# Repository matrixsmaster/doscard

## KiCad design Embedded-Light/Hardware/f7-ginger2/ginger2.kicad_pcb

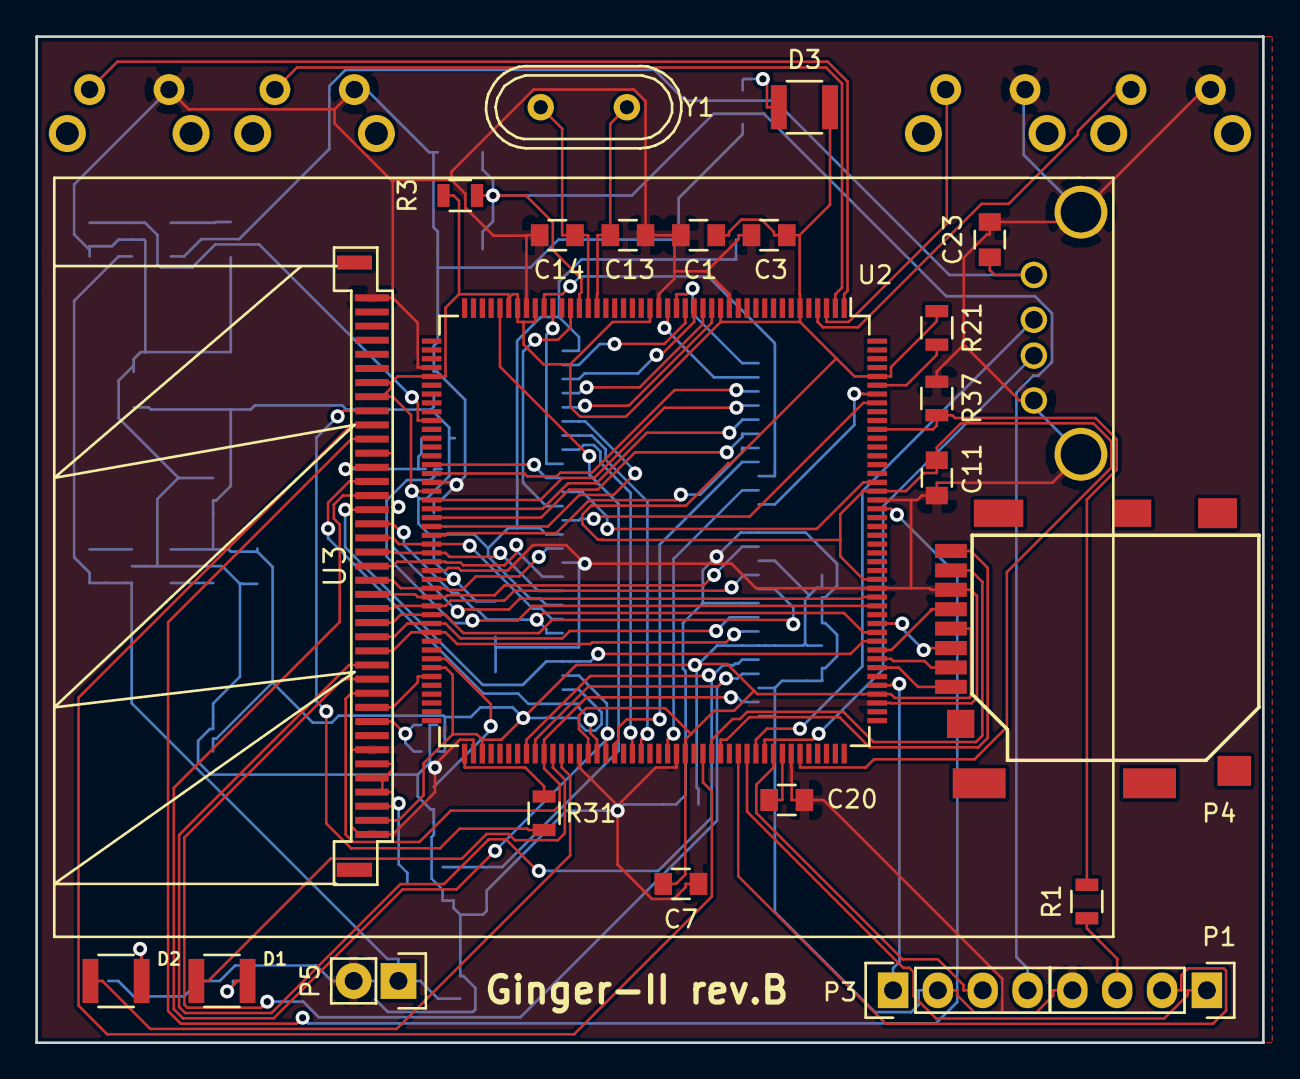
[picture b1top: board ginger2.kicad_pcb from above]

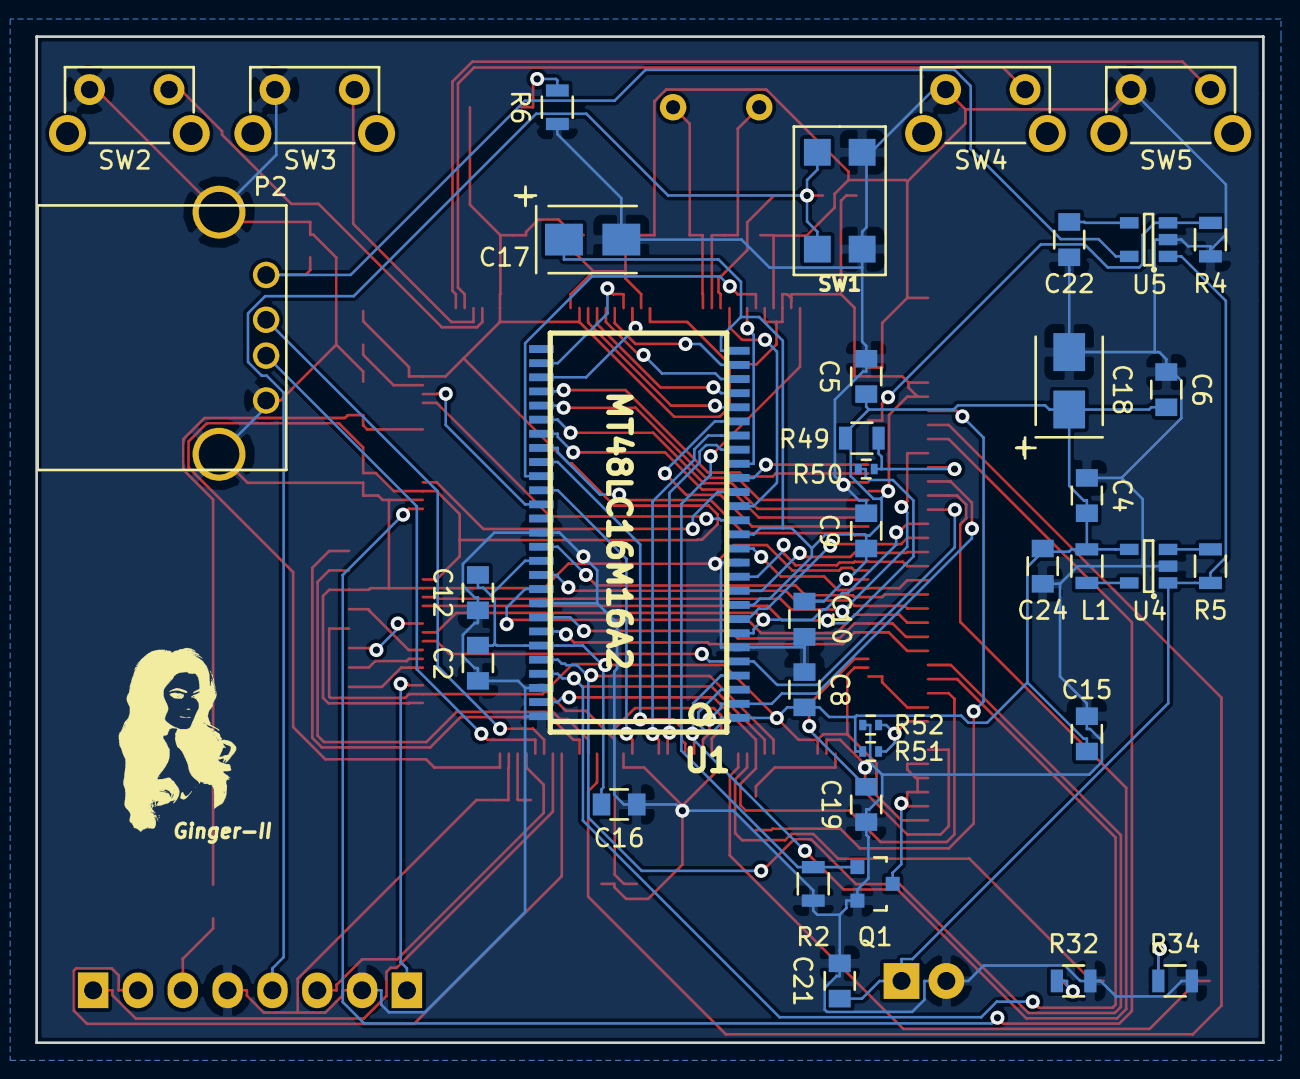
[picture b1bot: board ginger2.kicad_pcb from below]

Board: 2 copper layers, 69.5 x 57.0 mm, 60 parts (37 on the bottom side), 87 nets.

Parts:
C1, C2, C3, C4, C5, C6, C7, C8, C9, C10, C11, C12, C15, C16, C23: 100n; C_0805
C13, C14: 20p; C_0805
C17, C18: 47u; TantalC_SizeB_EIA-3528_Wave
C19, C20: 2.2u; C_0805
C21: 4.7u; C_0805
C22: 10n; C_0805
C24: 10u; C_0805
D1: LD1; R_1210
D2: LD2; R_1210
D3: PWR; R_1210
L1: 2.2uH; R_0805
P1: UART; Pin_Header_Straight_1x04
P2: USB_HOST; USB_A
P3: SWD; Pin_Header_Straight_1x04
P4: microSD
P5: BAT; Pin_Header_Straight_1x02
Q1: FDN337N; SOT-23
R1, R5, R31: 1k; R_0805
R2, R3, R4, R21, R37, R49: 10k; R_0805
R6: 510; R_0805
R32, R34: 330; R_0805
R50, R52: DNP; R_0402
R51: 0; R_0402
SW1: RST; but_7914G
SW2: B4; SW_Tactile_SPST_Angled
SW3: B3; SW_Tactile_SPST_Angled
SW4: B2; SW_Tactile_SPST_Angled
SW5: B1; SW_Tactile_SPST_Angled
U1: MT48LC16M16A2; TSOP-54
U2: STM32F767IIT6; LQFP-176_24x24mm_Pitch0.5mm
U3: WF24HTLAJDNN0; FPC_39
U4: LM3671MF-FIX; SOT-23-5
U5: LP2985LV; SOT-23-5
Y1: 20MHz; Crystal_HC49-U_Vertical

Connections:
+3V3: C1.1, C2.1, C3.1, C4.1, C5.1, C6.1, C7.1, C8.1, C9.1, C10.1, C11.1, C12.1, C15.1, C16.1, C17.1, C18.1, C24.1, D3.2, L1.2, P4.4, R3.1, R21.2, R49.2, R51.2, U1.1, U1.3, U1.9, U1.14, U1.27, U1.43, U1.49, U2.6, U2.15, U2.23, U2.36, U2.38, U2.39, U2.49, U2.62, U2.72, U2.82, U2.91, U2.103, U2.114, U2.127, U2.136, U2.149, U2.159, U2.172, U3.7, U3.8, U3.38, U4.4
+5V: C23.1, P2.1, U5.5
/LCD1_LK1: Q1.3, U3.34, U3.35, U3.36, U3.37
/cpu_boot: R1.1, R37.2, U2.166
/cpu_rst: P3.4, R3.2, SW1.2, U2.31
/sd_b0: P4.7, U2.117
/sd_b1: P4.8, U2.118
/sd_b2: P4.1, U2.139
/sd_b3: P4.2, U2.140
/sd_clk: P4.5, U2.141
/sd_cmd: P4.3, U2.144
/sdr_a0: U1.23, U2.16
/sdr_a1: U1.24, U2.17
/sdr_a2: U1.25, U2.18
/sdr_a3: U1.26, U2.19
/sdr_a4: U1.29, U2.20
/sdr_a5: U1.30, U2.21
/sdr_a6: U1.31, U2.60
/sdr_a7: U1.32, U2.63
/sdr_a8: U1.33, U2.64
/sdr_a9: U1.34, U2.65
/sdr_a10: U1.22, U2.66
/sdr_a11: U1.35, U2.67
/sdr_a12: U1.36, U2.106
/sdr_ba0: U1.20, U2.108
/sdr_ba1: U1.21, U2.109
/sdr_cas: U1.17, U2.160
/sdr_cke: U1.37, U2.35
/sdr_clk: U1.38, U2.112
/sdr_cs: U1.19, U2.34
/sdr_d0: U1.2, U2.104, U3.14
/sdr_d1: U1.4, U2.105, U3.15
/sdr_d2: U1.5, U2.142, U3.16
/sdr_d3: U1.7, U2.143, U3.17
/sdr_d4: U1.8, U2.68, U3.18
/sdr_d5: U1.10, U2.69, U3.19
/sdr_d6: U1.11, U2.70, U3.20
/sdr_d7: U1.13, U2.73, U3.21
/sdr_d8: U1.42, U2.74, U3.22
/sdr_d9: U1.44, U2.75, U3.23
/sdr_d10: U1.45, U2.76, U3.24
/sdr_d11: U1.47, U2.77, U3.25
/sdr_d12: U1.48, U2.78, U3.26
/sdr_d13: U1.50, U2.96, U3.27
/sdr_d14: U1.51, U2.97, U3.28
/sdr_d15: U1.53, U2.98, U3.29
/sdr_dqmh: U1.39, U2.170
/sdr_dqml: U1.15, U2.169
/sdr_ras: U1.18, U2.59
/sdr_we: U1.16, U2.32
/tft_cs: U2.116, U3.10
/tft_fsync: R31.1, U3.9
/tft_rd: R50.2, U2.146
/tft_rs: U2.157, U3.11
/tft_rst: U2.83, U3.30
/tft_wr: U2.147, U3.12
/usb_pon: R4.1, U2.54, U5.3
GND: C1.2, C2.2, C3.2, C4.2, C5.2, C6.2, C7.2, C8.2, C9.2, C10.2, C11.2, C12.2, C13.2, C14.2, C15.2, C16.2, C17.2, C18.2, C19.2, C20.1, C21.2, C22.2, C23.2, C24.2, P1.4, P2.4, P2.5, P3.2, P4.6, P5.2, Q1.2, R2.2, R4.2, R6.1, R32.2, R34.2, R37.1, R52.2, SW1.1, SW2.1, SW3.1, SW4.1, SW5.1, U1.6, U1.12, U1.41, U1.46, U1.52, U1.54, U2.14, U2.22, U2.37, U2.48, U2.61, U2.71, U2.90, U2.102, U2.113, U2.126, U2.135, U2.148, U2.158, U3.1, U3.33, U3.39, U4.2, U5.2
unnamed: C13.1, U2.29, Y1.1
unnamed: C14.1, U2.30, Y1.2
unnamed: C19.1, U2.81
unnamed: C20.2, U2.125
unnamed: C21.1, P5.1, R5.1, U4.1, U5.1
unnamed: C22.1, U5.4
unnamed: D1.1, R32.1
unnamed: D1.2, U2.99
unnamed: D2.1, R34.1
unnamed: D2.2, U2.100
unnamed: D3.1, R6.2
unnamed: L1.1, U4.5
unnamed: P1.1, U2.121
unnamed: P1.2, U2.120
unnamed: P1.3, R1.2
unnamed: P2.2, U2.122
unnamed: P2.3, U2.123
unnamed: P3.1, U2.137
unnamed: P3.3, U2.124
unnamed: Q1.1, R2.1, U2.40
unnamed: R5.2, U4.3
unnamed: R21.1, U2.171
unnamed: R31.2, U2.89
unnamed: R49.1, R50.1, U3.13
unnamed: R51.1, R52.1, U3.31
unnamed: SW2.2, U2.4
unnamed: SW3.2, U2.3
unnamed: SW4.2, U2.2
unnamed: SW5.2, U2.1

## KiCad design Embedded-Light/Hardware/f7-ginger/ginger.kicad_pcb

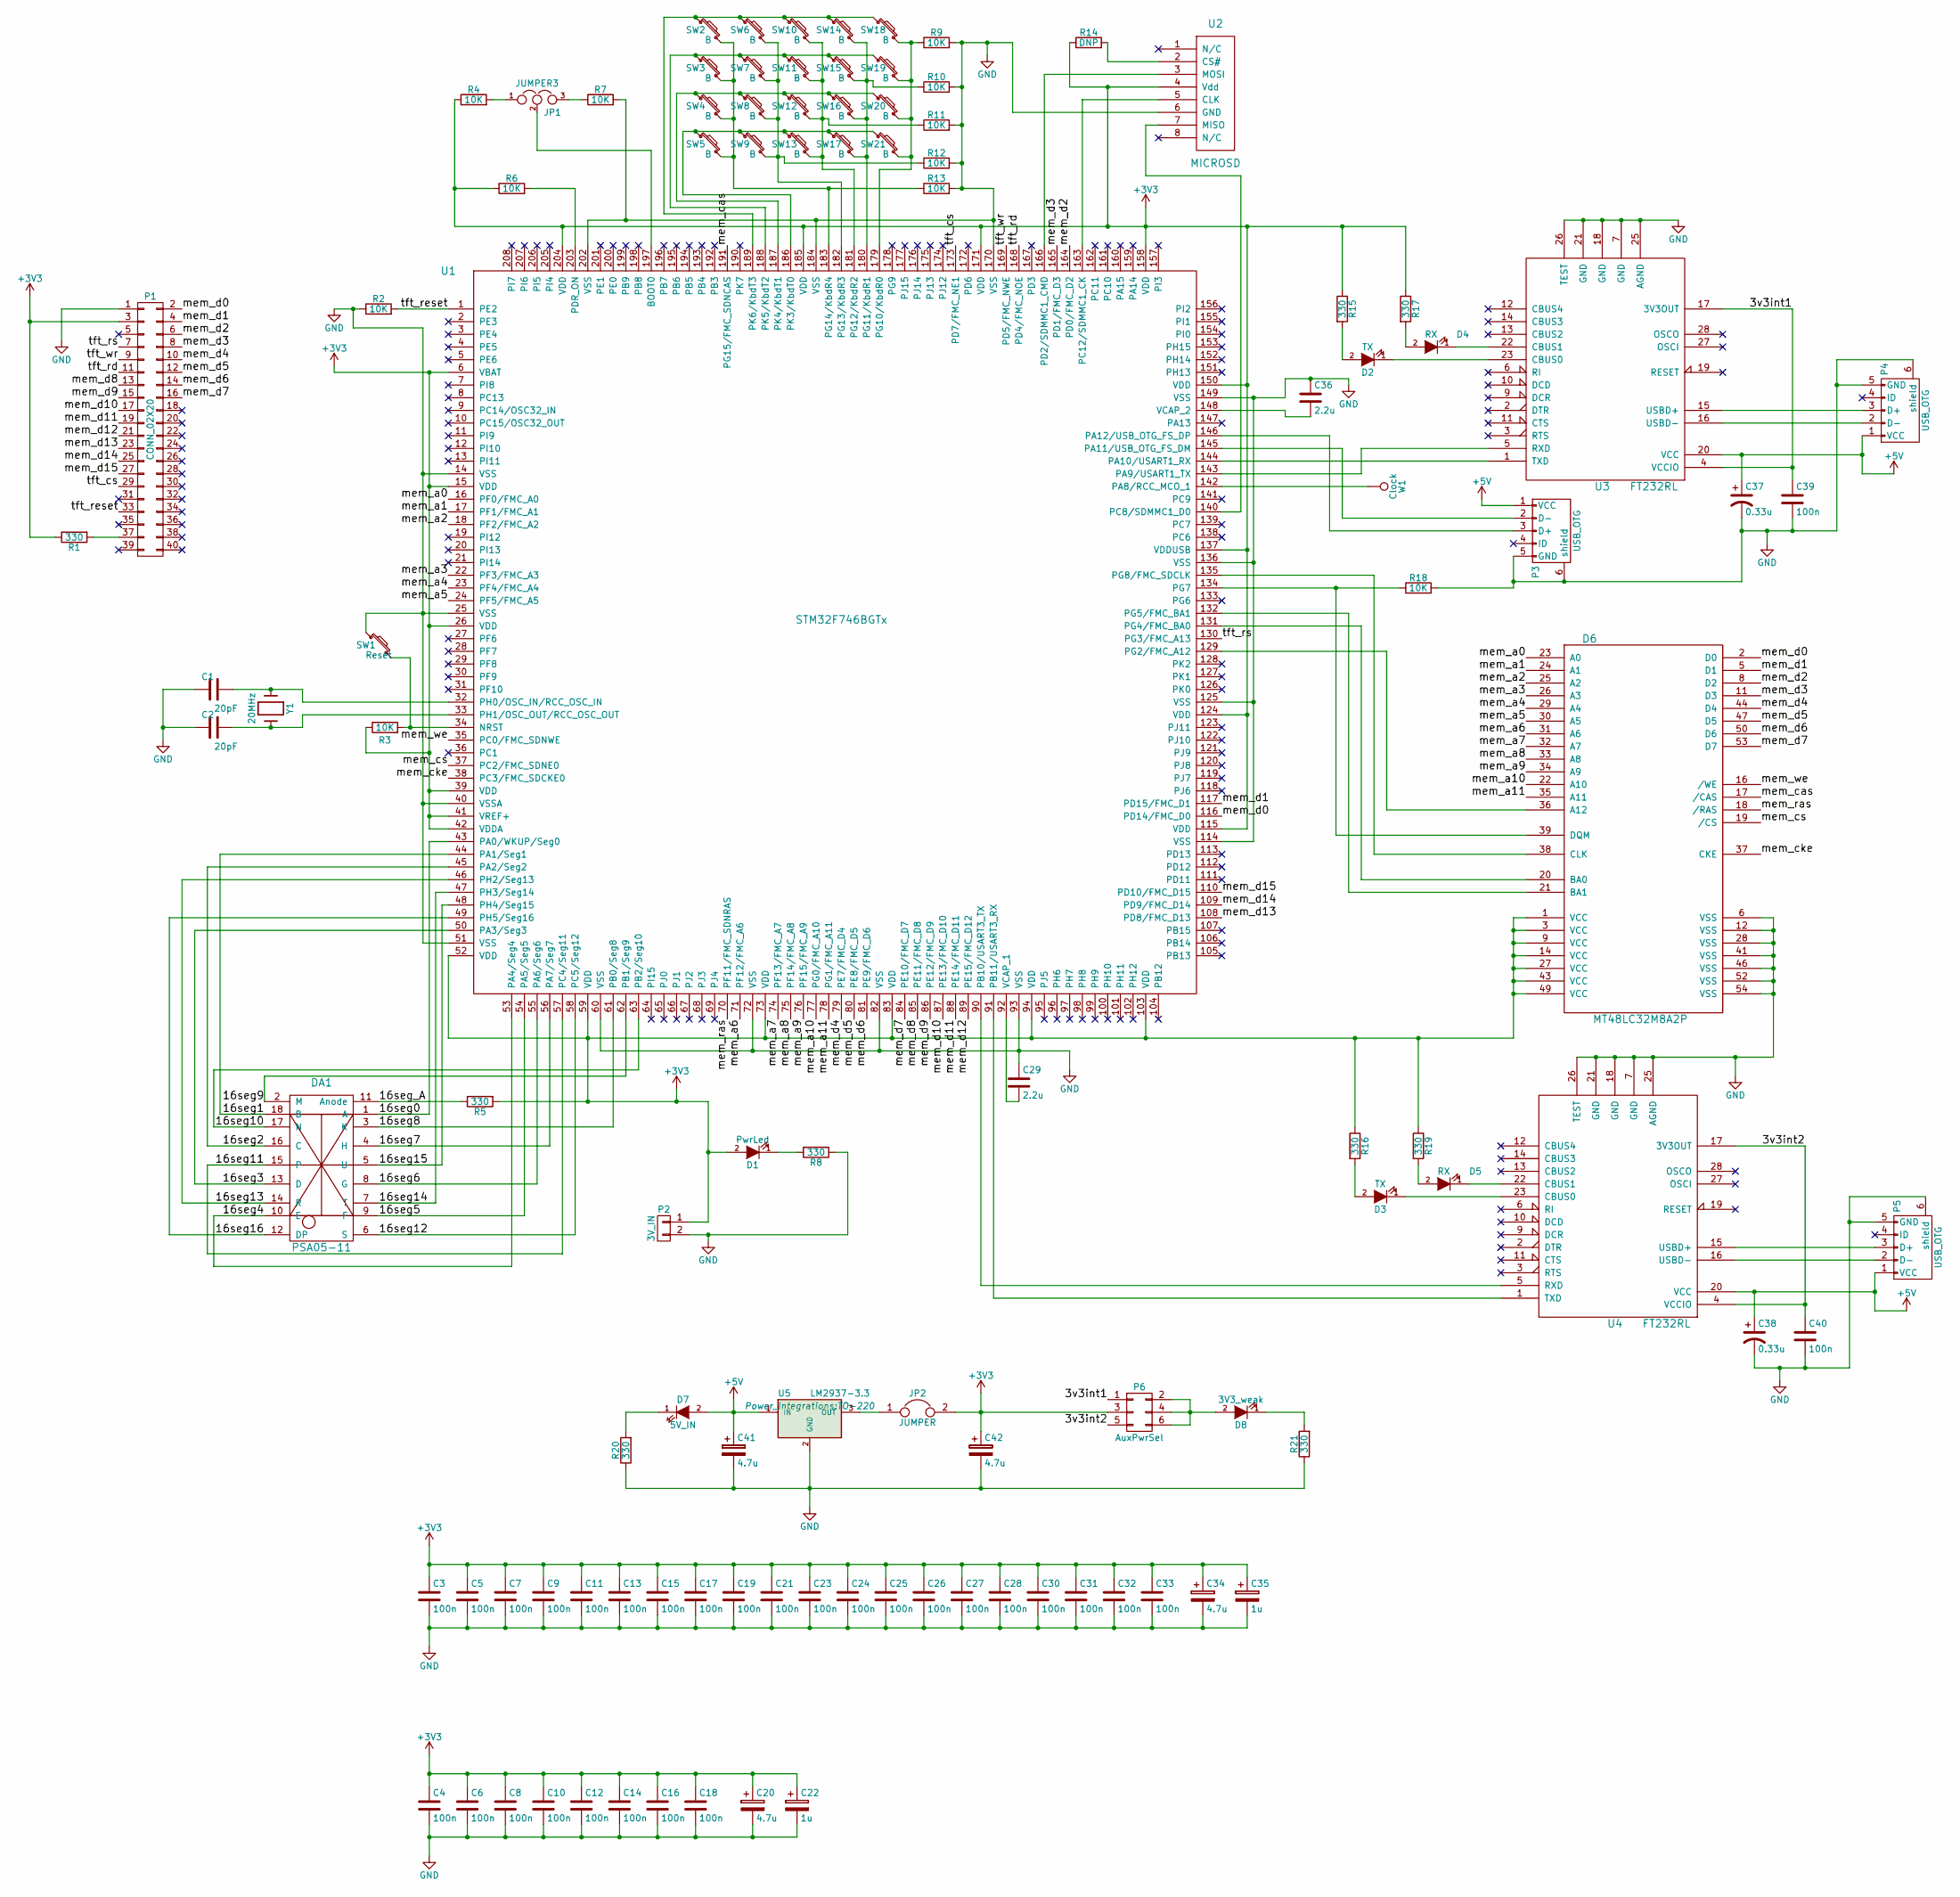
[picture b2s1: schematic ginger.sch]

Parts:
C1, C2: 20pF; C_0805
C3, C4, C5, C6, C7, C8, C9, C10, C11, C12, C13, C14, C15, C16, C17, C18, C19, C21, C23, C24, C25, C26, C27, C28, C30, C31, C32, C33, C39, C40: 100n; C_0805
C20, C34, C41, C42: 4.7u; TantalC_SizeB_EIA-3528_HandSoldering
C22, C35: 1u; TantalC_SizeB_EIA-3528_HandSoldering
C29, C36: 2.2u; C_0805
C37, C38: 0.33u; TantalC_SizeB_EIA-3528_HandSoldering
D1: PwrLed; R_1210
D2, D3: TX; R_1210
D4, D5: RX; R_1210
D6: MT48LC32M8A2P; TSOP-54
D7: 5V_IN; R_1210
D8: 3V3_weak; R_1210
DA1: PSA05-11
JP1: JUMPER3; Pin_Header_Straight_1x03
JP2: JUMPER; Pin_Header_Straight_1x02
P1: CONN_02X20; Pin_Header_Straight_2x20
P2: 3V_IN; Pin_Header_Straight_1x02
P3, P4, P5: USB_OTG; USB_Mini-B
P6: AuxPwrSel; Pin_Header_Straight_2x03
R1, R5, R8, R15, R16, R17, R19, R20, R21: 330; R_0805
R2, R3, R4, R6, R7, R9, R10, R11, R12, R13, R18: 10K; R_0805
R14: DNP; R_0805
SW1: Reset; but_7914G
SW2, SW3, SW4, SW5, SW6, SW7, SW8, SW9, SW10, SW11, SW12, SW13, SW14, SW15, SW16, SW17, SW18, SW19, SW20, SW21: B; but_7914G
U1: STM32F746BGTx; QFP_208
U2: MICROSD; microSD
U3, U4: FT232RL; SSOP-28_5.3x10.2mm_Pitch0.65mm
U5: LM2937-3.3; TO-220
W1: Clock; Pin_Header_Straight_1x01
Y1: 20MHz; Crystal_HC49-U_Vertical

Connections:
+3V3: C3.1, C4.1, C5.1, C6.1, C7.1, C8.1, C9.1, C10.1, C11.1, C12.1, C13.1, C14.1, C15.1, C16.1, C17.1, C18.1, C19.1, C20.1, C21.1, C22.1, C23.1, C24.1, C25.1, C26.1, C27.1, C28.1, C30.1, C31.1, C32.1, C33.1, C34.1, C35.1, C42.1, D1.2 (A), D6.1 (VCC), D6.3 (VCC), D6.9 (VCC), D6.14 (VCC), D6.27 (VCC), D6.43 (VCC), D6.49 (VCC), JP2.2, P1.3, P2.1, P6.3, R1.1, R3.1, R4.1, R5.2, R6.1, R14.1, R15.1, R16.1, R17.1, R19.1, U1.6 (VBAT), U1.15 (VDD), U1.26 (VDD), U1.39 (VDD), U1.41 (VREF+), U1.42 (VDDA), U1.52 (VDD), U1.59 (VDD), U1.73 (VDD), U1.83 (VDD), U1.94 (VDD), U1.103 (VDD), U1.115 (VDD), U1.124 (VDD), U1.137 (VDDUSB), U1.150 (VDD), U1.158 (VDD), U1.171 (VDD), U1.185 (VDD), U1.204 (VDD), U2.4 (Vdd)
+5V: C37.1, C38.1, C41.1, D7.2 (A), P3.1 (VCC), P4.1 (VCC), P5.1 (VCC), U3.20 (VCC), U4.20 (VCC), U5.1 (IN)
/3v3int1: C39.1, P6.1, U3.4 (VCCIO), U3.17 (3V3OUT)
/3v3int2: C40.1, P6.5, U4.4 (VCCIO), U4.17 (3V3OUT)
/16seg0: DA1.1 (A), U1.43 (PA0/WKUP/Seg0)
/16seg1: DA1.18 (B), U1.44 (PA1/Seg1)
/16seg2: DA1.16 (C), U1.45 (PA2/Seg2)
/16seg3: DA1.13 (D), U1.50 (PA3/Seg3)
/16seg4: DA1.10 (E), U1.53 (PA4/Seg4)
/16seg5: DA1.9 (F), U1.54 (PA5/Seg5)
/16seg6: DA1.8 (G), U1.55 (PA6/Seg6)
/16seg7: DA1.4 (H), U1.56 (PA7/Seg7)
/16seg8: DA1.3 (K), U1.61 (PB0/Seg8)
/16seg9: DA1.2 (M), U1.62 (PB1/Seg9)
/16seg10: DA1.17 (N), U1.63 (PB2/Seg10)
/16seg11: DA1.15, U1.57 (PC4/Seg11)
/16seg12: DA1.6 (S), U1.58 (PC5/Seg12)
/16seg13: DA1.14 (R), U1.46 (PH2/Seg13)
/16seg14: DA1.7 (T), U1.47 (PH3/Seg14)
/16seg15: DA1.5 (U), U1.48 (PH4/Seg15)
/16seg16: DA1.12 (DP), U1.49 (PH5/Seg16)
/16seg_A: DA1.11 (Anode), R5.1
/mem_a0: D6.23 (A0), U1.16 (PF0/FMC_A0)
/mem_a1: D6.24 (A1), U1.17 (PF1/FMC_A1)
/mem_a2: D6.25 (A2), U1.18 (PF2/FMC_A2)
/mem_a3: D6.26 (A3), U1.22 (PF3/FMC_A3)
/mem_a4: D6.29 (A4), U1.23 (PF4/FMC_A4)
/mem_a5: D6.30 (A5), U1.24 (PF5/FMC_A5)
/mem_a6: D6.31 (A6), U1.71 (PF12/FMC_A6)
/mem_a7: D6.32 (A7), U1.74 (PF13/FMC_A7)
/mem_a8: D6.33 (A8), U1.75 (PF14/FMC_A8)
/mem_a9: D6.34 (A9), U1.76 (PF15/FMC_A9)
/mem_a10: D6.22 (A10), U1.77 (PG0/FMC_A10)
/mem_a11: D6.35 (A11), U1.78 (PG1/FMC_A11)
/mem_cas: D6.17 (/CAS), U1.191 (PG15/FMC_SDNCAS)
/mem_cke: D6.37 (CKE), U1.38 (PC3/FMC_SDCKE0)
/mem_cs: D6.19 (/CS), U1.37 (PC2/FMC_SDNE0)
/mem_d0: D6.2 (D0), P1.2, U1.116 (PD14/FMC_D0)
/mem_d1: D6.5 (D1), P1.4, U1.117 (PD15/FMC_D1)
/mem_d2: D6.8 (D2), P1.6, U1.164 (PD0/FMC_D2)
/mem_d3: D6.11 (D3), P1.8, U1.165 (PD1/FMC_D3)
/mem_d4: D6.44 (D4), P1.10, U1.79 (PE7/FMC_D4)
/mem_d5: D6.47 (D5), P1.12, U1.80 (PE8/FMC_D5)
/mem_d6: D6.50 (D6), P1.14, U1.81 (PE9/FMC_D6)
/mem_d7: D6.53 (D7), P1.16, U1.84 (PE10/FMC_D7)
/mem_d8: P1.13, U1.85 (PE11/FMC_D8)
/mem_d9: P1.15, U1.86 (PE12/FMC_D9)
/mem_d10: P1.17, U1.87 (PE13/FMC_D10)
/mem_d11: P1.19, U1.88 (PE14/FMC_D11)
/mem_d12: P1.21, U1.89 (PE15/FMC_D12)
/mem_d13: P1.23, U1.108 (PD8/FMC_D13)
/mem_d14: P1.25, U1.109 (PD9/FMC_D14)
/mem_d15: P1.27, U1.110 (PD10/FMC_D15)
/mem_ras: D6.18 (/RAS), U1.70 (PF11/FMC_SDNRAS)
/mem_we: D6.16 (/WE), U1.35 (PC0/FMC_SDNWE)
/tft_cs: P1.29, U1.173 (PD7/FMC_NE1)
/tft_rd: P1.11, U1.168 (PD4/FMC_NOE)
/tft_reset: P1.33, R2.2, U1.1 (PE2)
/tft_rs: P1.7, U1.130 (PG3/FMC_A13)
/tft_wr: P1.9, U1.169 (PD5/FMC_NWE)
GND: C1.2, C2.2, C3.2, C4.2, C5.2, C6.2, C7.2, C8.2, C9.2, C10.2, C11.2, C12.2, C13.2, C14.2, C15.2, C16.2, C17.2, C18.2, C19.2, C20.2, C21.2, C22.2, C23.2, C24.2, C25.2, C26.2, C27.2, C28.2, C29.1, C30.2, C31.2, C32.2, C33.2, C34.2, C35.2, C36.1, C37.2, C38.2, C39.2, C40.2, C41.2, C42.2, D6.6 (VSS), D6.12 (VSS), D6.28 (VSS), D6.41 (VSS), D6.46 (VSS), D6.52 (VSS), D6.54 (VSS), P1.1, P2.2, P3.5 (GND), P3.6 (shield), P4.5 (GND), P4.6 (shield), P5.5 (GND), P5.6 (shield), R2.1, R7.2, R8.1, R9.2, R10.2, R11.2, R12.2, R13.2, R18.2, R20.1, R21.1, SW1.1, U1.14 (VSS), U1.25 (VSS), U1.40 (VSSA), U1.51 (VSS), U1.60 (VSS), U1.72 (VSS), U1.82 (VSS), U1.93 (VSS), U1.114 (VSS), U1.125 (VSS), U1.136 (VSS), U1.149 (VSS), U1.170 (VSS), U1.184 (VSS), U1.202 (VSS), U2.6 (GND), U3.7 (GND), U3.18 (GND), U3.21 (GND), U3.25 (AGND), U3.26 (TEST), U4.7 (GND), U4.18 (GND), U4.21 (GND), U4.25 (AGND), U4.26 (TEST), U5.2 (GND)
unnamed: C1.1, U1.32 (PH0/OSC_IN/RCC_OSC_IN), Y1.1
unnamed: C2.1, U1.33 (PH1/OSC_OUT/RCC_OSC_OUT), Y1.2
unnamed: C29.2, U1.92 (VCAP_1)
unnamed: C36.2, U1.148 (VCAP_2)
unnamed: D1.1 (K), R8.2
unnamed: D2.1 (K), U3.23 (CBUS0)
unnamed: D2.2 (A), R15.2
unnamed: D3.1 (K), U4.23 (CBUS0)
unnamed: D3.2 (A), R16.2
unnamed: D4.1 (K), U3.22 (CBUS1)
unnamed: D4.2 (A), R17.2
unnamed: D5.1 (K), U4.22 (CBUS1)
unnamed: D5.2 (A), R19.2
unnamed: D6.20 (BA0), U1.131 (PG4/FMC_BA0)
unnamed: D6.21 (BA1), U1.132 (PG5/FMC_BA1)
unnamed: D6.36 (A12), U1.129 (PG2/FMC_A12)
unnamed: D6.38 (CLK), U1.135 (PG8/FMC_SDCLK)
unnamed: D6.39 (DQM), R18.1, U1.134 (PG7)
unnamed: D7.1 (K), R20.2
unnamed: D8.1 (K), R21.2
unnamed: D8.2 (A), P6.2, P6.4, P6.6
unnamed: JP1.1, R4.2
unnamed: JP1.2, U1.197 (BOOT0)
unnamed: JP1.3, R7.1
unnamed: JP2.1, U5.3 (OUT)
unnamed: P1.37, R1.2
unnamed: P3.2 (D-), U1.145 (PA11/USB_OTG_FS_DM)
unnamed: P3.3 (D+), U1.146 (PA12/USB_OTG_FS_DP)
unnamed: P4.2 (D-), U3.16 (USBD-)
unnamed: P4.3 (D+), U3.15 (USBD+)
unnamed: P5.2 (D-), U4.16 (USBD-)
unnamed: P5.3 (D+), U4.15 (USBD+)
unnamed: R3.2, SW1.2, U1.34 (NRST)
unnamed: R6.2, U1.203 (PDR_ON)
unnamed: R9.1, SW18.2, SW19.2, SW20.2, SW21.2, U1.179 (PG10/KbdR0)
unnamed: R10.1, SW14.2, SW15.2, SW16.2, SW17.2, U1.180 (PG11/KbdR1)
unnamed: R11.1, SW10.2, SW11.2, SW12.2, SW13.2, U1.181 (PG12/KbdR2)
unnamed: R12.1, SW6.2, SW7.2, SW8.2, SW9.2, U1.182 (PG13/KbdR3)
unnamed: R13.1, SW2.2, SW3.2, SW4.2, SW5.2, U1.183 (PG14/KbdR4)
unnamed: R14.2, U2.2 (CS#)
unnamed: SW2.1, SW6.1, SW10.1, SW14.1, SW18.1, U1.189 (PK6/KbdT3)
unnamed: SW3.1, SW7.1, SW11.1, SW15.1, SW19.1, U1.188 (PK5/KbdT2)
unnamed: SW4.1, SW8.1, SW12.1, SW16.1, SW20.1, U1.187 (PK4/KbdT1)
unnamed: SW5.1, SW9.1, SW13.1, SW17.1, SW21.1, U1.186 (PK3/KbdT0)
unnamed: U1.90 (PB10/USART3_TX), U4.5 (RXD)
unnamed: U1.91 (PB11/USART3_RX), U4.1 (TXD)
unnamed: U1.140 (PC8/SDMMC1_D0), U2.7 (MISO)
unnamed: U1.142 (PA8/RCC_MCO_1), W1.1
unnamed: U1.143 (PA9/USART1_TX), U3.5 (RXD)
unnamed: U1.144 (PA10/USART1_RX), U3.1 (TXD)
unnamed: U1.163 (PC12/SDMMC1_CK), U2.5 (CLK)
unnamed: U1.166 (PD2/SDMMC1_CMD), U2.3 (MOSI)

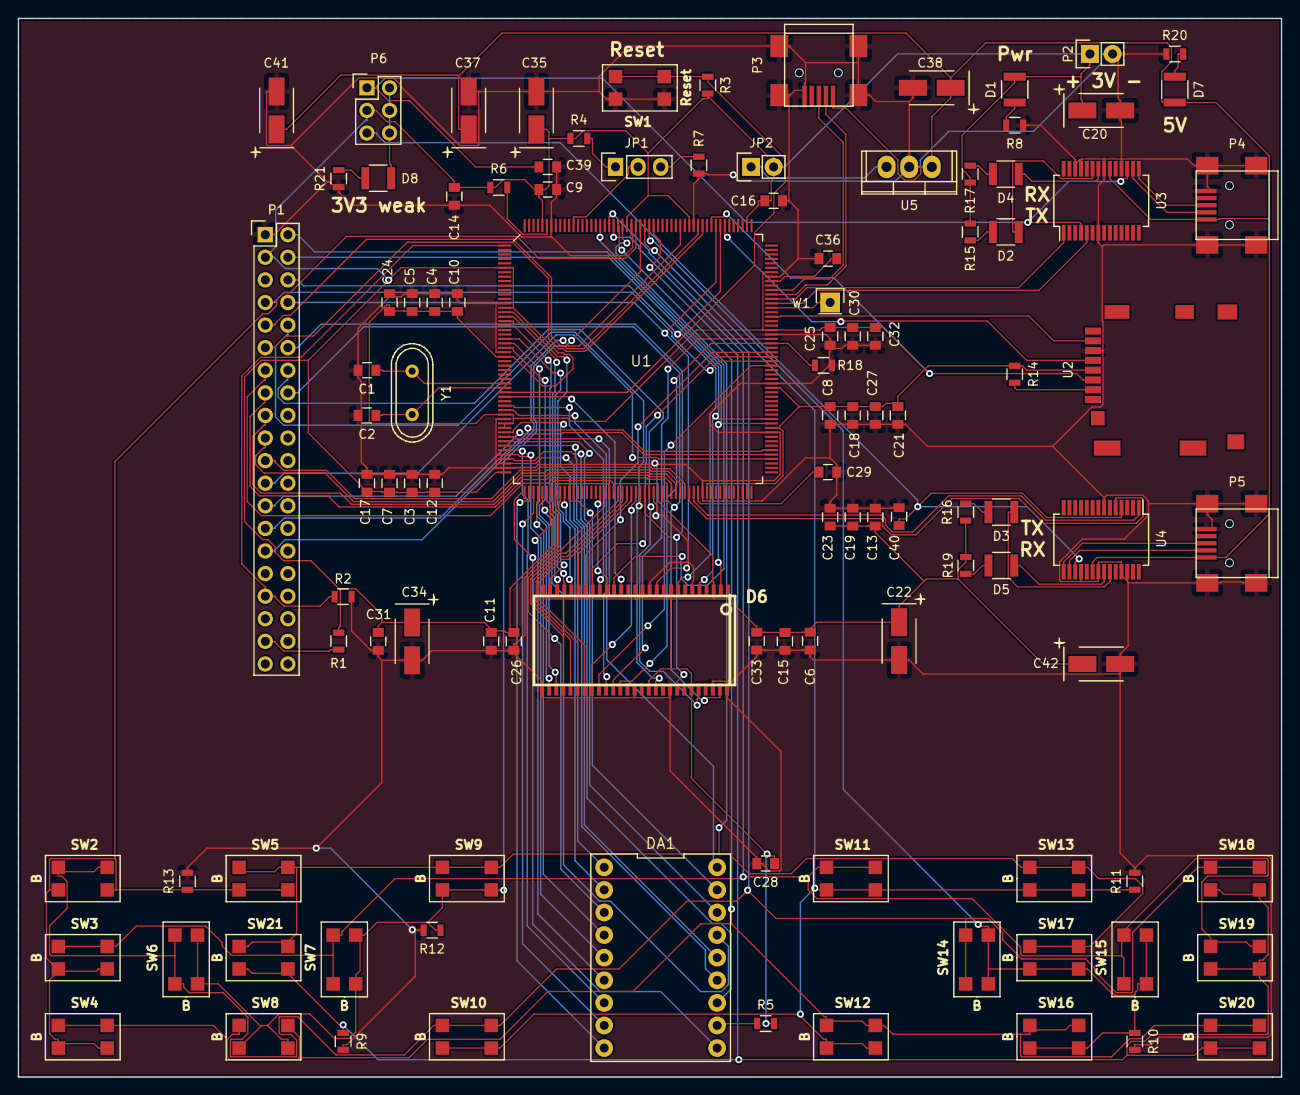
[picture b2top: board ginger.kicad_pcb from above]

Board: 2 copper layers, 142.0 x 119.0 mm, 108 parts (0 on the bottom side), 113 nets.

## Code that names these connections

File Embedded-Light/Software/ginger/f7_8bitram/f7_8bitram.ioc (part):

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Mcu.Name=STM32F746B(E-G)Tx
Mcu.Package=LQFP208
Mcu.UserName=STM32F746BGTx
PA0/WKUP.GPIOParameters=GPIO_Label
PA0/WKUP.GPIO_Label=Seg0
PA0/WKUP.Signal=GPIO_Output
PA1.GPIOParameters=GPIO_Label
PA1.GPIO_Label=Seg1
PA1.Signal=GPIO_Output
PA10.Mode=Asynchronous
PA10.Signal=USART1_RX
PA11.Mode=Device_Only
PA11.Signal=USB_OTG_FS_DM
PA12.Mode=Device_Only
PA12.Signal=USB_OTG_FS_DP
PA13.Mode=Serial_Wire
PA13.Signal=SYS_JTMS-SWDIO
PA14.Mode=Serial_Wire
PA14.Signal=SYS_JTCK-SWCLK
PA2.GPIOParameters=GPIO_Label
PA2.GPIO_Label=Seg2
PA2.Signal=GPIO_Output
PA3.GPIOParameters=GPIO_Label
PA3.GPIO_Label=Seg3
PA3.Signal=GPIO_Output
PA4.GPIOParameters=GPIO_Label
PA4.GPIO_Label=Seg4
PA4.Signal=GPIO_Output
PA5.GPIOParameters=GPIO_Label
PA5.GPIO_Label=Seg5
PA5.Signal=GPIO_Output
PA6.GPIOParameters=GPIO_Label
PA6.GPIO_Label=Seg6
PA6.Signal=GPIO_Output
PA7.GPIOParameters=GPIO_Label
PA7.GPIO_Label=Seg7
PA7.Signal=GPIO_Output
PA8.GPIOParameters=GPIO_Speed
PA8.GPIO_Speed=GPIO_SPEED_FREQ_VERY_HIGH
PA8.Mode=Clock-out-1
PA8.Signal=RCC_MCO_1
PA9.Mode=Asynchronous
PA9.Signal=USART1_TX
PB0.GPIOParameters=GPIO_Label
PB0.GPIO_Label=Seg8
PB0.Signal=GPIO_Output
PB1.GPIOParameters=GPIO_Label
PB1.GPIO_Label=Seg9
PB1.Signal=GPIO_Output
PB10.Mode=Asynchronous
PB10.Signal=USART3_TX
PB11.Mode=Asynchronous
PB11.Signal=USART3_RX
PB2.GPIOParameters=GPIO_Label
PB2.GPIO_Label=Seg10
PB2.Signal=GPIO_Output
PC0.Signal=FMC_SDNWE
PC12.GPIOParameters=GPIO_PuPd
PC12.GPIO_PuPd=GPIO_NOPULL
PC12.Mode=SD_1_bit
PC12.Signal=SDMMC1_CK
PC2.Mode=SdramChipSelect1_1
PC2.Signal=FMC_SDNE0
PC3.Mode=SdramChipSelect1_1
PC3.Signal=FMC_SDCKE0
PC4.GPIOParameters=GPIO_Label
PC4.GPIO_Label=Seg11
PC4.Signal=GPIO_Output
PC5.GPIOParameters=GPIO_Label
PC5.GPIO_Label=Seg12
PC5.Signal=GPIO_Output
PC8.GPIOParameters=GPIO_PuPd
PC8.GPIO_PuPd=GPIO_PULLUP
PC8.Mode=SD_1_bit
PC8.Signal=SDMMC1_D0
PD0.Signal=FMC_D2_DA2
PD1.Signal=FMC_D3_DA3
PD10.Signal=FMC_D15_DA15
PD14.Signal=FMC_D0_DA0
PD15.Signal=FMC_D1_DA1
PD2.GPIOParameters=GPIO_PuPd
PD2.GPIO_PuPd=GPIO_PULLUP
PD2.Mode=SD_1_bit
PD2.Signal=SDMMC1_CMD
PD4.Signal=FMC_NOE
PD5.Signal=FMC_NWE
PD7.Mode=NorPsramChipSelect1_1
PD7.Signal=FMC_NE1
PD8.Signal=FMC_D13_DA13
PD9.Signal=FMC_D14_DA14
PE10.Signal=FMC_D7_DA7
PE11.Signal=FMC_D8_DA8
PE12.Signal=FMC_D9_DA9
PE13.Signal=FMC_D10_DA10
PE14.Signal=FMC_D11_DA11
PE15.Signal=FMC_D12_DA12
PE2.GPIOParameters=GPIO_Label
PE2.GPIO_Label=TFT_Reset
PE2.Signal=GPIO_Output
PE6.Signal=FMC_A22
PE7.Signal=FMC_D4_DA4
PE8.Signal=FMC_D5_DA5
PE9.Signal=FMC_D6_DA6
PF0.Signal=FMC_A0
PF1.Signal=FMC_A1
PF11.Signal=FMC_SDNRAS
PF12.Signal=FMC_A6
PF13.Signal=FMC_A7
PF14.Signal=FMC_A8
PF15.Signal=FMC_A9
PF2.Signal=FMC_A2
PF3.Signal=FMC_A3
PF4.Signal=FMC_A4
PF5.Signal=FMC_A5
PG0.Signal=FMC_A10
PG1.Signal=FMC_A11
PG10.GPIOParameters=GPIO_Label
PG10.GPIO_Label=KbdR0
PG10.Signal=GPIO_Input
PG11.GPIOParameters=GPIO_Label
PG11.GPIO_Label=KbdR1
PG11.Signal=GPIO_Input
PG12.GPIOParameters=GPIO_Label
PG12.GPIO_Label=KbdR2
PG12.Signal=GPIO_Input
PG13.GPIOParameters=GPIO_Label
PG13.GPIO_Label=KbdR3
PG13.Signal=GPIO_Input
PG14.GPIOParameters=GPIO_Label
PG14.GPIO_Label=KbdR4
PG14.Signal=GPIO_Input
PG15.Signal=FMC_SDNCAS
PG2.Signal=FMC_A12
PG3.GPIOParameters=GPIO_Label
PG3.GPIO_Label=TFT_RS
PG3.Signal=GPIO_Output
PG4.Signal=FMC_A14_BA0
PG5.Signal=FMC_A15_BA1
PG7.GPIOParameters=GPIO_Label
PG7.GPIO_Label=SDRAM_DQM
PG7.Signal=GPIO_Output
PG8.Signal=FMC_SDCLK
PH0/OSC_IN.Mode=HSE-External-Oscillator
PH0/OSC_IN.Signal=RCC_OSC_IN
PH1/OSC_OUT.Mode=HSE-External-Oscillator
PH1/OSC_OUT.Signal=RCC_OSC_OUT
PH2.GPIOParameters=GPIO_Label
PH2.GPIO_Label=Seg13
PH2.Signal=GPIO_Output
PH3.GPIOParameters=GPIO_Label
PH3.GPIO_Label=Seg14
PH3.Signal=GPIO_Output
PH4.GPIOParameters=GPIO_Label
PH4.GPIO_Label=Seg15
PH4.Signal=GPIO_Output
PH5.GPIOParameters=GPIO_Label
PH5.GPIO_Label=Seg16
PH5.Signal=GPIO_Output
PK3.GPIOParameters=GPIO_Label
PK3.GPIO_Label=KbdT0
PK3.Signal=GPIO_Output
PK4.GPIOParameters=GPIO_Label
PK4.GPIO_Label=KbdT1
PK4.Signal=GPIO_Output
PK5.GPIOParameters=GPIO_Label
PK5.GPIO_Label=KbdT2
PK5.Signal=GPIO_Output
PK6.GPIOParameters=GPIO_Label
PK6.GPIO_Label=KbdT3
PK6.Signal=GPIO_Output
RCC.HSE_VALUE=20000000
RCC.SYSCLKFreq_VALUE=216000000
RCC.SYSCLKSource=RCC_SYSCLKSOURCE_PLLCLK
board=f7_8bitram

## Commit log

2013-12-29 Initial upload
2013-12-29 Uploading second test
2013-12-29 Current test Updated
2013-12-29 Experiments with building
2013-12-29 More experiments
2013-12-29 libgui_tk removed
2013-12-29 softmodem removed
2013-12-29 IPX removed
2013-12-29 new line
2013-12-31 More building experiments
2013-12-31 New makefile
2014-01-01 Some sound hardware deprecated
2014-01-01 Begin dev for ARM
2014-01-02 Update and move fpu
2014-01-02 add profiler stub
2014-01-03 instrumentation experiments begins
2014-01-03 instrument.cpp works
2014-01-03 Instrumentation works like a supercharged 5L Jag, eeehaw
2014-01-03 sdl becomes static
2014-01-03 LAST SDL1.2 VERSION
2014-01-03 Add SDL2
2014-01-04 sdl2 works
2014-01-04 big update
2014-01-26 next step
2014-01-26 gui removed
2014-01-26 thr up
2014-01-27 render compiles
2014-01-30 compiled successfully
2014-01-30 init works
2014-01-30 add xsupport
2014-02-01 some minor replaces
2014-02-02 various changes
2014-02-02 timer OK
2014-02-02 image pipe OK
2014-02-02 IT'S ALIVE
2014-02-02 begin impl new FIO
2014-02-02 todo updated
2014-02-02 new fio compiles
2014-02-03 fio finished
2014-02-03 update fio impl
2014-02-04 mutexes doesnt work this way
2014-02-04 but they works this way
2014-02-05 keyboard works
2014-02-05 cue sheets works
2014-02-06 dlck still present
2014-02-06 sdl thr testing
2014-02-07 testing threads continued
2014-02-07 remove trash
2014-02-07 mutex syscall lock detected in testing program
2014-02-07 atomic sem in test works
2014-02-07 atomic sem in xshell works too
2014-02-08 faster operations
2014-02-08 cleanup
2014-02-08 w95 loaded in 800x600
2014-02-09 threads exits ok
2014-02-09 box IDE project files moved up
2014-02-09 debug code temporarily removed
2014-02-09 big refactor begins
2014-02-09 big refactor update
2014-02-09 refactor update
2014-02-09 remove obsolete SDLS
2014-02-09 namespace refactoring complete
2014-02-10 sound works ok
2014-02-10 joystick removed
2014-02-10 GUS and GB is gone
2014-02-10 top refactored, compiles, but events broken
2014-02-10 events fixed, a little problem with paging persist
2014-02-10 do not use this
2014-02-11 bug localized. do not use this rev
2014-02-11 FIXED
2014-02-11 small makefiles fix
2014-02-11 biggest refactoring begin
2014-02-11 refactoring update
2014-02-14 rollback to 96
2014-02-14 rollback to 95
2014-02-14 rebuilding init model
2014-02-14 rs232 src cleanup
2014-02-14 sound config change
2014-02-14 modify dos init procedure
2014-02-15 some cleanup
2014-02-15 clear() functions added and tested
2014-02-15 setup functions and module base cleanup
2014-02-15 try to clean violations
2014-02-15 host-oriented render pipe impl ok
2014-02-15 adaptive frameskip implemented
2014-02-15 add skip limiter
2014-02-27 cross remove config clean
2014-02-27 small update
2014-02-27 work with stat()s begin
2014-02-28 some vga code cleanup
2014-02-28 stat implementation tested
2014-02-28 fio update
2014-02-28 stats moved
2014-03-01 small fixes
2014-03-01 dirs control refactor
2014-03-01 MSG system refactor
2014-03-01 time system reviewed
2014-03-01 timer_delay impl
2014-03-01 minor refactor
2014-03-01 ldb now fully independent of xshell
2014-03-01 new projects
2014-03-02 removing static sdl2
2014-03-02 removed sdl2
2014-03-02 llvm setup isnt ready yet
2014-03-02 llvm link success
2014-03-02 minor update
2014-03-02 major update
2014-03-02 alive
2014-03-02 function lookup is working
2014-03-02 function call is working
2014-03-03 new library loading code
2014-03-03 constructor fail fixed
2014-03-04 ldbcard works
2014-03-04 add log
2014-03-05 experiments upd
2014-03-05 problem with exit() fixed with a kludge
2014-03-05 UI stub working
2014-03-05 UI update
2014-03-05 xshell2 shows frames
2014-03-06 UI works
2014-03-06 new quit procedure
2014-03-07 final cleanup
2014-03-09 fixing paths
2014-03-09 build paths fixed
2014-03-10 some new functions
2014-03-10 new ldb API: add some stubs
2014-03-11 small arranging update
2014-03-12 implement some stubs
2014-03-13 new callback interface tested
2014-03-13 cleaning
2014-03-13 clean complete
2014-03-13 one of the vector bugs fixed
2014-03-13 cleanup after bugfix
2014-03-13 more API fixes and stout works
2014-03-17 fix console input
2014-03-17 stdin fix
2014-03-18 headless code cleanup
2014-03-22 datetime fix and minor clean
2014-03-24 add new VM modes
2014-03-24 pause mode fix
2014-03-24 update sound works
2014-03-27 direct sound works but lags
2014-03-27 changes to sound wrapper
2014-03-30 DNU - broken sync
2014-04-01 new syncs
2014-06-12 minor conflicts resolved
2014-12-08 box-mt started +name fix
2014-12-09 unnecessary classes removal in progress
2014-12-09 end cleanup
2014-12-09 box-MT preliminary structure
2014-12-10 arm branch tested
2014-12-11 temp. drop of box-mt; also dep info add
2014-12-11 move box-mt to branches
2014-12-11 new branch explained
2014-12-12 cbox update
2015-03-14 DNU: tried to fix llvm sync system, unsuccess
2015-03-14 gitignore added
2015-03-14 testing revert - sync works with LLVM 3.3 without sound
2015-03-15 tested successfully with llvm-3.4
2015-03-15 update - still no big effect (possible cause - LLVM version)
2015-03-15 uniform versions
2015-03-15 master branch successfully moved
2015-03-15 new libdoscard directory structure
2015-03-15 ldc-st makefiles now works
2015-03-15 conditional instrumentation in libdosbox
2015-03-15 corrected informational headers
2015-03-15 tested compilation with mingw
2015-03-16 DNU - prepare for export to vs
2015-03-17 initial windows build ok
2015-03-17 mingw build works, but just barely
2015-03-21 Windows build works, two major memory problems fixed.
2015-03-21 debug printing removed
2015-03-21 stabilizing
2015-03-23 Interleaved mode added and successfully tested in Unix
2015-03-23 LDB headers unified
2015-03-25 interleave mode fix
2015-03-27 in progress: add facility to post-process video frames inside libdoscard
2015-03-29 in progress: scaling seems to be working
2015-03-29 xshell2: add args parser; ldb: frame processor still in progress
2015-03-29 frame processor seems to be working
2015-03-29 post-processing added to w32 wrapper
2015-03-29 inclusion fix for VS
2015-03-30 added UnlockSpeed() function
2015-03-30 minor fixes
2015-12-24 8086tiny added
2015-12-24 Small fixes to VM86 code.
2018-05-21 Last changes to old t86 branch.
2018-05-21 Project revived
2018-05-21 F4DISCO: code moved from temporary debug placeholder into os.c
2018-05-22 F4DISCO: Added VM wrapper from my FO4 DOS mod.
2018-05-22 F4DISCO: Added new font data. Text is rendered correctly now.
2018-05-22 [DNU] F4DISCO: trying to add rudimentary USB host functionality.
2018-05-24 [DNU] F4DISCO: trying to add rudimentary USB host functionality. Part2/2.
2018-05-24 First hardware project added.
2018-05-24 Claudette: updated
2018-05-27 Claudette: F7 floorplan updated
2018-05-29 Claudette: added pinout sheet for main MCU
2018-05-30 F7DISCO: added CubeMX config
2018-05-30 F4DISCO: USB host changes reverted back.
2018-05-31 Added F7 discovery test. Not yet useable.
2018-05-31 F7DISCO: added sdmmc+fatfs test project using very old CubeMX HAL. The fatfs bug is gone now.
2018-06-01 F7DISCO: regenerated with newest CubeMX HAL. Added a lot of debug output. Fixed card-detection bug (PC13 is in floating state, and R12 is missing). The fatfs bug seems to be gone now.
2018-06-01 Maintenance update. Temporary F7 project deleted.
2018-06-01 F7DISCO: debug output removed. Card detect kludge inserted.
2018-06-22 F7DISCO: added LTDC and SDRAM support. Test OK.
2018-06-22 F7DISCO: added SDIO->SDRAM test.
2018-06-22 F7DISCO: VM code added, SAI removed, FatFS extended functions enabled.
2018-06-22 F7DISCO: pixel font added and tested.
2018-06-22 F7DISCO: font rendering now uses Chrome-ART.
2018-06-22 F7DISCO: added DMA2D string printer test.
2018-06-23 [DNU] F7DISCO: HardFault at unaligned SDRAM access detected.
2018-07-08 Hardware: added super-simple f7-based Ginger test board.
2018-07-08 Ginger: updated schematics to the current real board state.
2018-07-08 Ginger: added software repository for the board testing.
2018-07-08 Removed obsolete Readme file.
2018-07-08 Ginger: 8 MB SDRAM boundary bug fixed.
2018-07-09 Ginger: schematic sheet updated with TODOs.
2018-07-09 Ginger: keyboard tested.
2018-07-09 Ginger: added playback controls and first alpha symbols for virtual keyboard are now displayable on the 16-seg indicator.
2018-07-10 Added STM32CubeMX -> KiCAD symbol converter tool.
2018-07-10 Ginger: MPU, optimizations and caching are enabled and they works.
2018-07-10 Ginger: timings fixed, unaligned access is tested successfully this time.
2018-07-10 Ginger: TFT display module supplier link added to BOM.
2018-07-10 Ginger: first char from FreeDOS banner are showed up.
2018-07-11 Ginger board: added note about RXTX LEDs.
2018-07-11 Added current status report.
2018-07-11 Status update for Windows platform.
2018-07-11 F7DISCO: MPU enabled, some excessive debug output removed.
2018-07-11 F7DISCO: FreeDOS boots up.
2018-07-11 F7DISCO: text rendering temporarily fixed with a kludge; VCPU major speedup achieved. The operating speed is now acceptable.
2018-07-11 F7DISCO: text rendering issues are fixed.
2018-07-11 Ginger: OS boots up most of the time, but SDRAM interface is very unstable. Need timing adjustment and init sequence correction.
2018-07-11 Status updated.
2018-07-12 F7DISCO: added keyboard support. VM input is not yet active though.
2018-07-12 F7DISCO: speedup and keyboard input. FreeDOS is totally useable now on Discovery board.
2018-08-18 Ginger-2: added
2018-08-19 Ginger-2: added hardware
2018-08-19 Ginger2: minor fixes, board is a bit stable now.
2018-08-19 Status: updated.
2018-08-22 Ginger2: added OSD stub for virtual keyboard.
2018-08-22 Ginger2: virtual keyboard is alive, VM is temporarily disabled.
2018-08-22 Ginger2: VK works
2018-08-23 [DNU] Ginger2: JPEG hardware decoding experiments. Partial success.
2018-08-23 [DNU] Ginger2: more JPEG experiments.
2018-08-23 Ginger2: the board is useable now.
2018-08-26 Ginger2: new board schematics and placement, ready to route.
2018-08-26 Ginger2: rev.B routed.
2019-02-24 Ginger2: graphics is working
2019-02-24 Ginger2: VM86 virtual devices infrastructure backported from SGUI project
2019-02-24 Ginger2: changes for presentation mode
2019-03-24 LDB: maintenance update
2019-03-24 Ginger-2: updated schematics for future board revision
2019-03-24 Claudette project superseded by H7-based Helga
2019-03-27 Helga: moving partially finished schematics from Ginger-II
2019-03-27 HW: docs updated
2019-03-27 Helga: schematics updated
2019-03-27 Helga: added simple audio amplifier
2019-03-31 Helga: updated
2019-05-26 PC version update
2020-11-05 Added license files
